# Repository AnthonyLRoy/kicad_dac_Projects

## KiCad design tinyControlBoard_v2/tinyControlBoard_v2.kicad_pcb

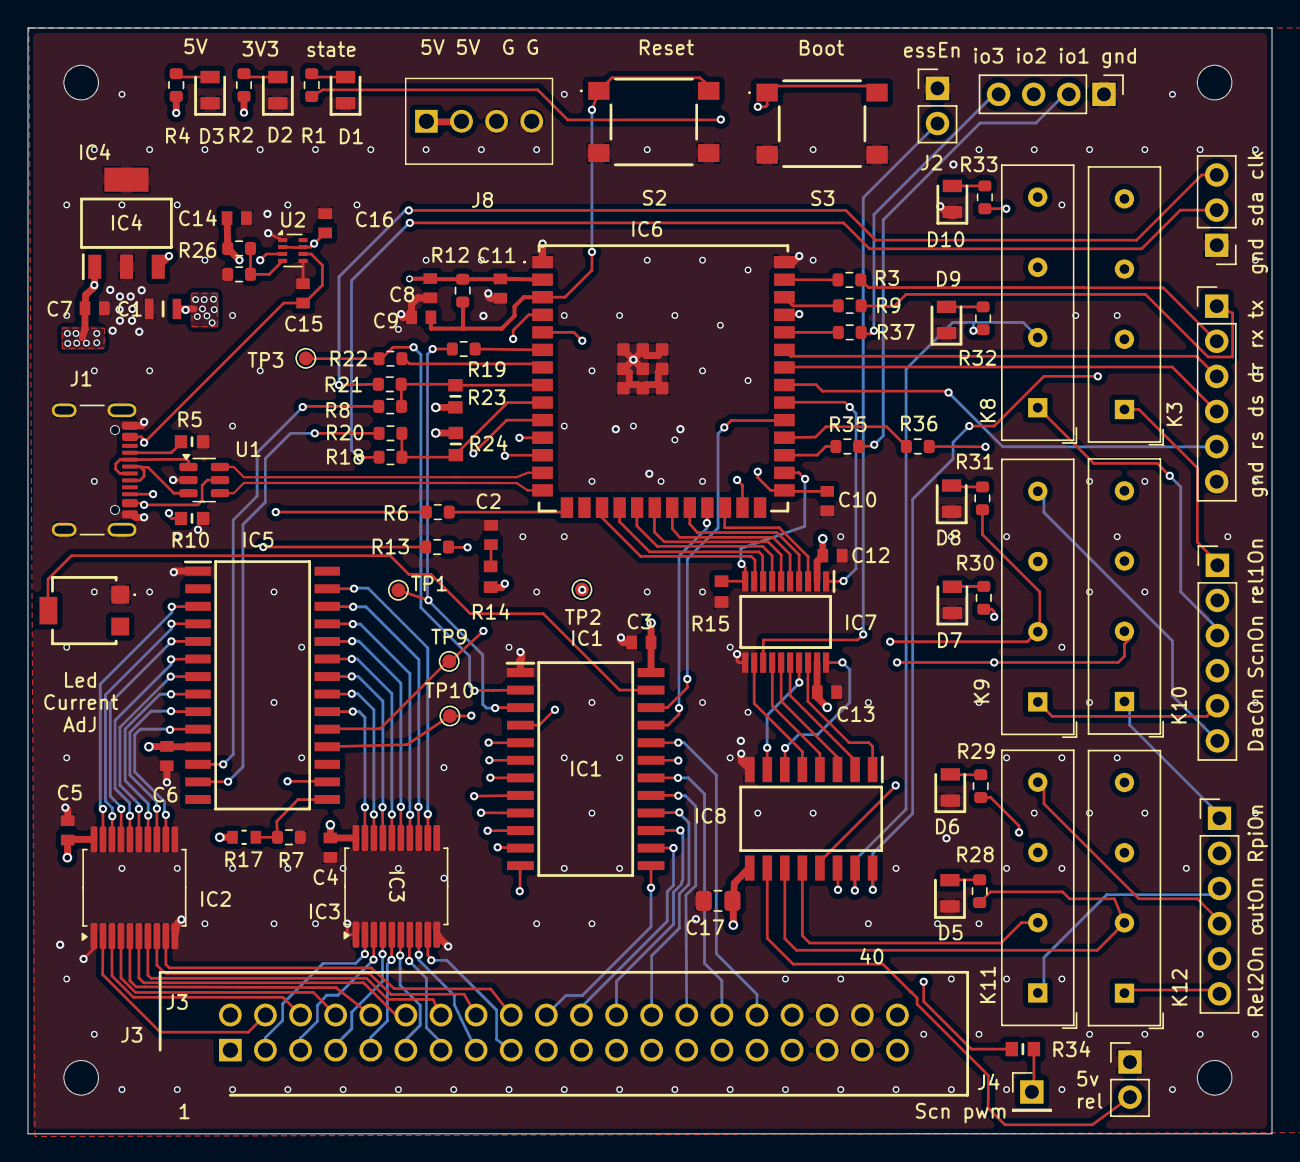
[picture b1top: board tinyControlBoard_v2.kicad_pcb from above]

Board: 6 copper layers, 90.0 x 80.0 mm, 99 parts (0 on the bottom side), 146 nets.

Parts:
C1: 33u; CAPC2012X145N
C2, C8: 10u; CAPC1608X90N
C3, C4, C5, C6, C9, C10, C11, C12, C13: 0u1; CAPC1608X87N
C7: 47u; CAPC1608X90N
C14, C15, C16: 1u; CAPC1608X90N
C17: 100n; C_0805_2012Metric_Pad1.18x1.45mm_HandSolder
D1, D2: LG_R971-KN-1; LEDC2012X80N
D3, D5, D6, D7, D8, D9, D10: LS_R976; LEDC2012X40N
H1, H2, H3, H4: MountingHole; MountingHole_2.5mm
IC1: STP16CPC26MTR; SOIC127P1032X265-24N
IC2, IC3: MAX6818EAP+T; SSOP-20_5.3x7.2mm_P0.65mm
IC4: LM3940IMPX-3.3; SOT230P700X180-4N
IC5: MCP23018-E_SO; SOIC127P1030X265-28N
IC6: ESP32-S3-WROOM-1U-N16; ESP32S3WROOM1UN16
IC7: TXS0108EPWRG4; SOP65P640X120-20N
IC8: ULN2003LVDR; SOIC127P780X200-16N
J1: USB_C_Receptacle_USB2.0_16P; USB_C_Receptacle_GCT_USB4105-xx-A_16P_TopMnt_Horizontal
J2, J11: Conn_01x02_Pin; PinHeader_1x02_P2.54mm_Vertical
J3: 70246-4001; SHDR40W64P254_2X20_5842X889X947P
J4: Conn_01x01_Socket; PinHeader_1x01_P2.54mm_Vertical
J5, J7, J9: Buffer; PinHeader_1x06_P2.54mm_Vertical
J6: Conn_01x04_Pin; PinHeader_1x04_P2.54mm_Vertical
J8: 1725672
J10: Conn_01x03_Pin; PinHeader_1x03_P2.54mm_Vertical
K3, K8, K9, K10, K11, K12: SIL05-1A72-71D; Relay_SPST_StandexMeder_SIL_Form1A
R1, R2: 100R; R_0603_1608Metric
R3, R8, R9, R18, R19, R20, R21, R22, R35, R36, R37: 22R; R_0603_1608Metric
R4, R6, R13: 300R; R_0603_1608Metric
R5, R10: 5K1; RESC1608X55N
R7: MCT0603PD1001DP500; R_0603_1608Metric
R12: 10K; R_0603_1608Metric
R14, R15: 10K; RESC1608X50N
R17: TNPW060315K0BEEA; RESC1608X60N
R23, R24: 4k7; RESC1609X55N
R25: 330k; R_0603_1608Metric
R26: 100k; R_0603_1608Metric
R28, R29, R30, R31, R32, R33: 1k; R_0603_1608Metric
R34: 22R; RESC1609X55N
S2, S3: 430182043816
TP1, TP2, TP3, TP9, TP10: S2761-46R; TestPoint_Pad_D1.0mm
U1: USBLC6-2SC6; SOT-23-6
U2: TPS2116DRL; SOT-583-8
VR1: 3214G-1-103E; 3214G1103E

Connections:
+3V3: C1.2, C3.2, C4.1, C5.2, C6.1, C8.1, C11.1, C12.1, IC1.24 (VDD), IC2.20 (VCC), IC3.20 (VCC), IC4.3 (OUT), IC5.11 (VDD), IC6.2 (3V3), IC7.2 (VCCA), R2.1, R12.1, R14.1, R17.1, R23.2, R24.2
+5V: C7.1, C13.1, C16.1, C17.2, IC4.1 (IN), IC7.19 (VCCB), IC8.9 (COM), J3.39, J3.40, K3.5, K8.5, K9.5, K10.5, K11.5, K12.5, R4.1, U2.2 (VOUT), U2.7 (VOUT)
/5v_io: IC6.22 (IO14), IC7.4 (A3)
/5v_io_ext: IC8.10 (OUT7), J11.2
/5v_io_out: IC7.17 (B3), IC8.7 (IN7)
/BOOT: C10.1, IC6.27 (IO0), S3.1 (COM_1), S3.3 (COM_2)
/EN: C9.1, IC6.3 (EN), R12.2, S2.1 (COM_1), S2.3 (COM_2)
/GPIO_01: IC6.39 (IO1), R3.1
/GPIO_02: IC6.38 (IO2), R9.1
/Gen2_on_ext: IC8.11 (OUT6), K12.3, R28.1
/Gen_1_on_ext: IC8.16 (OUT1), K3.3, R33.1
/Generic_io_1: IC6.29 (IO36), R35.1
/Generic_io_2: IC6.30 (IO37), R36.1
/Generic_io_3: IC6.36 (RXD0), R37.1
/I2c_sda_ext: J10.2, R18.1
/IntA: IC5.19 (INTA), IC6.11 (IO18), TP9.1 (1_1)
/Intb: IC5.18 (INTB), IC6.12 (IO8), TP10.1 (1_1)
/Serial Rx: J9.2, R3.2
/Serial Tx: J9.1, R9.2
/USB_5V: C15.1, J1.A4 (VBUS), J1.A9 (VBUS), J1.B4 (VBUS), J1.B9 (VBUS), U1.5 (VBUS), U2.6 (VIN2)
/USB_N: IC6.13 (IO19), U1.6 (I/O1)
/USB_P: IC6.14 (IO20), U1.4 (I/O2)
/addr_exp: IC5.15 (ADDR), R7.1, R17.2
/app_active: IC6.25 (IO48), R1.1
/btn_in_1: IC2.2 (IN1), J3.4
/btn_in_2: IC2.3 (IN2), J3.6
/btn_in_3: IC2.4 (IN3), J3.8
/btn_in_4: IC2.5 (IN4), J3.10
/btn_in_5: IC2.6 (IN5), J3.12
/btn_in_6: IC2.7 (IN6), J3.14
/btn_in_7: IC2.8 (IN7), J3.16
/btn_in_8: IC2.9 (IN8), J3.18
/btn_in_9: IC3.2 (IN1), J3.3
/btn_in_10: IC3.3 (IN2), J3.5
/btn_in_11: IC3.4 (IN3), J3.7
/btn_in_12: IC3.5 (IN4), J3.9
/btn_in_13: IC3.6 (IN5), J3.11
/btn_in_14: IC3.7 (IN6), J3.13
/btn_in_15: IC3.8 (IN7), J3.15
/btn_in_16: IC3.9 (IN8), J3.17
/btn_l_1: IC2.19 (OUT1), IC5.3 (GPB0)
/btn_l_2: IC2.18 (OUT2), IC5.4 (GPB1)
/btn_l_3: IC2.17 (OUT3), IC5.5 (GPB2)
/btn_l_4: IC2.16 (OUT4), IC5.6 (GPB3)
/btn_l_5: IC2.15 (OUT5), IC5.7 (GPB4)
/btn_l_6: IC2.14 (OUT6), IC5.8 (GPB5)
/btn_l_7: IC2.13 (OUT7), IC5.9 (GPB6)
/btn_l_8: IC2.12 (OUT8), IC5.10 (GPB7)
/btn_l_9: IC3.19 (OUT1), IC5.20 (GPA0)
/btn_l_10: IC3.18 (OUT2), IC5.21 (GPA1)
/btn_l_11: IC3.17 (OUT3), IC5.22 (GPA2)
/btn_l_12: IC3.16 (OUT4), IC5.23 (GPA3)
/btn_l_13: IC3.15 (OUT5), IC5.24 (GPA4)
/btn_l_14: IC3.14 (OUT6), IC5.25 (GPA5)
/btn_l_15: IC3.13 (OUT7), IC5.26 (GPA6)
/btn_l_16: IC3.12 (OUT8), IC5.27 (GPA7)
/dac_power: IC6.20 (IO12), IC7.6 (A5)
/dac_power_on_a: J5.5, K9.1
/dac_power_on_b: J5.6, K9.7
/dac_power_on_ext: IC8.14 (OUT3), K9.3, R31.1
/dac_power_out: IC7.15 (B5), IC8.3 (IN3)
/esp_ir_sent: IC6.34 (IO41), J9.4
/g_io_1: J6.2, R35.2
/g_io_2: J6.3, R36.2
/g_io_3: J6.4, R37.2
/gen2_a: J7.5, K12.7
/gen2_b: J7.6, K12.1
/gen_1_a: J5.1, K3.1
/gen_1_b: J5.2, K3.7
/i2c_clk: IC6.8 (IO15), R8.2, R21.2, R23.1
/i2c_clk_ext: J10.3, R21.1
/i2c_clk_int: IC5.12 (SCL), R8.1
/i2c_reset: IC5.16 (~RESET), IC6.10 (IO17)
/i2c_sda: IC6.9 (IO16), R18.2, R20.2, R24.1
/i2c_sda_int: IC5.13 (SDA), R20.1
/led_o_1: IC1.5 (OUT0), J3.19
/led_o_2: IC1.6 (OUT1), J3.21
/led_o_3: IC1.7 (OUT2), J3.23
/led_o_4: IC1.8 (OUT3), J3.25
/led_o_5: IC1.9 (OUT4), J3.27
/led_o_6: IC1.10 (OUT5), J3.29
/led_o_7: IC1.11 (OUT6), J3.31
/led_o_8: IC1.12 (OUT7), J3.33
/led_o_9: IC1.13 (OUT8), J3.20
/led_o_10: IC1.14 (OUT9), J3.22
/led_o_11: IC1.15 (OUT10), J3.24
/led_o_12: IC1.16 (OUT11), J3.26
/led_o_13: IC1.17 (OUT12), J3.28
/led_o_14: IC1.18 (OUT13), J3.30
/led_o_15: IC1.19 (OUT14), J3.34
/led_o_16: IC1.20 (OUT15), J3.32
/monitor_bright: IC6.37 (TXD0), R34.1
/on_led: IC6.15 (IO3), R6.1
/output_power_on_a: J7.3, K11.1
/output_power_on_b: J7.4, K11.7
/output_power_on_ext: IC8.12 (OUT5), K11.3, R29.1
/output_stage: IC6.17 (IO9), IC7.9 (A8)
/output_stage_out: IC7.12 (B8), IC8.5 (IN5)
/protodac_en: IC6.18 (IO10), IC7.8 (A7)
/protodac_en_out: IC7.13 (B7), J2.2
/relay_enable: IC6.28 (IO35), IC7.10 (OE), R15.1
/relay_gen_1: IC6.24 (IO47), IC7.3 (A2)
/relay_gen_1_out: IC7.18 (B2), IC8.1 (IN1)
/relay_gen_2: IC6.32 (IO39), IC7.1 (A1)
/relay_get_2_out: IC7.20 (B1), IC8.6 (IN6)
/rpi4_data_ready: IC6.35 (IO42), J9.3
/rpi_power: IC6.19 (IO11), IC7.7 (A6)
/rpi_power_on_a: J7.1, K10.1
/rpi_power_on_b: J7.2, K10.7
/rpi_power_on_ext: IC8.13 (OUT4), K10.3, R30.1
/rpi_power_out: IC7.14 (B6), IC8.4 (IN4)
/rpi_state: IC6.33 (IO40), J9.5
/screen_on: IC6.21 (IO13), IC7.5 (A4)
/screen_on_a: J5.3, K8.1
/screen_on_b: J5.4, K8.7
/screen_on_ext: IC8.15 (OUT2), K8.3, R32.1
/screen_on_out: IC7.16 (B4), IC8.2 (IN2)
/standby_led: IC6.4 (IO4), R13.2
/stp_clk: IC1.3 (CLK), R19.1, TP1.1 (1_1)
/stp_le: IC1.4 (LE), IC6.5 (IO5), TP2.1 (1_1)
/stp_pwm: IC1.21 (~OE), IC6.23 (IO21)
/stp_sdi: IC1.2 (SDI), R22.1, TP3.1 (1_1)
/stp_sdo: IC1.22 (SDO), IC6.31 (IO38)
GND: C1.1, C2.2, C3.1, C4.2, C5.1, C6.2, C7.2, C8.2, C9.2, C10.2, C11.2, C12.2, C13.2, C14.2, C15.2, C16.2, C17.1, D1.1 (K), D2.1 (K), D3.1 (K), D5.1 (K), D6.1 (K), D7.1 (K), D8.1 (K), D9.1 (K), D10.1 (K), IC1.1 (GND), IC2.1 (~EN), IC2.10 (GND), IC3.1 (~EN), IC3.10 (GND), IC4.2 (GND_1), IC4.4 (GND_2), IC5.1 (VSS), IC6.1 (GND_1), IC6.40 (GND_2), IC6.41 (GND_3), IC6.42 (GND_4), IC6.43 (GND_5), IC6.44 (GND_6), IC6.45 (GND_7), IC6.46 (GND_8), IC6.47 (GND_9), IC6.48 (GND_10), IC6.49 (GND_11), IC7.11 (GND), IC8.8 (GND), J1.A1 (GND), J1.A12 (GND), J1.B1 (GND), J1.B12 (GND), J1.S1 (SHIELD), J2.1, J3.35, J3.36, J3.37, J3.38, J6.1, J8.3, J8.4, J9.6, J10.1, J11.1, R5.2, R7.2, R10.2, R15.2, R26.1, S2.2 (NO_1), S2.4 (NO_2), S3.2 (NO_1), S3.4 (NO_2), U1.2 (GND), U2.1 (GND), U2.5 (MODE), VR1.1 (CCW)
unnamed: C2.1, R14.2
unnamed: D1.2 (A), R1.2
unnamed: D2.2 (A), R2.2
unnamed: D3.2 (A), R4.2
unnamed: D5.2 (A), R28.2
unnamed: D6.2 (A), R29.2
unnamed: D7.2 (A), R30.2
unnamed: D8.2 (A), R31.2
unnamed: D9.2 (A), R32.2
unnamed: D10.2 (A), R33.2
unnamed: IC1.23 (R-EXT), VR1.2 (WIPER)
unnamed: IC6.6 (IO6), R19.2
unnamed: IC6.7 (IO7), R22.2
unnamed: J1.A5 (CC1), R5.1
unnamed: J1.B5 (CC2), R10.1
unnamed: J1.A6 (D+), J1.B6 (D+), U1.3 (I/O2)
unnamed: J1.A7 (D-), J1.B7 (D-), U1.1 (I/O1)
unnamed: J3.1, R6.2
unnamed: J3.2, R13.1
unnamed: J4.1 (Pin_1_1), R34.2
unnamed: R25.2, R26.2, U2.4 (PR1)
VCC: C14.1, J8.1, J8.2, R25.1, U2.3 (VIN1)

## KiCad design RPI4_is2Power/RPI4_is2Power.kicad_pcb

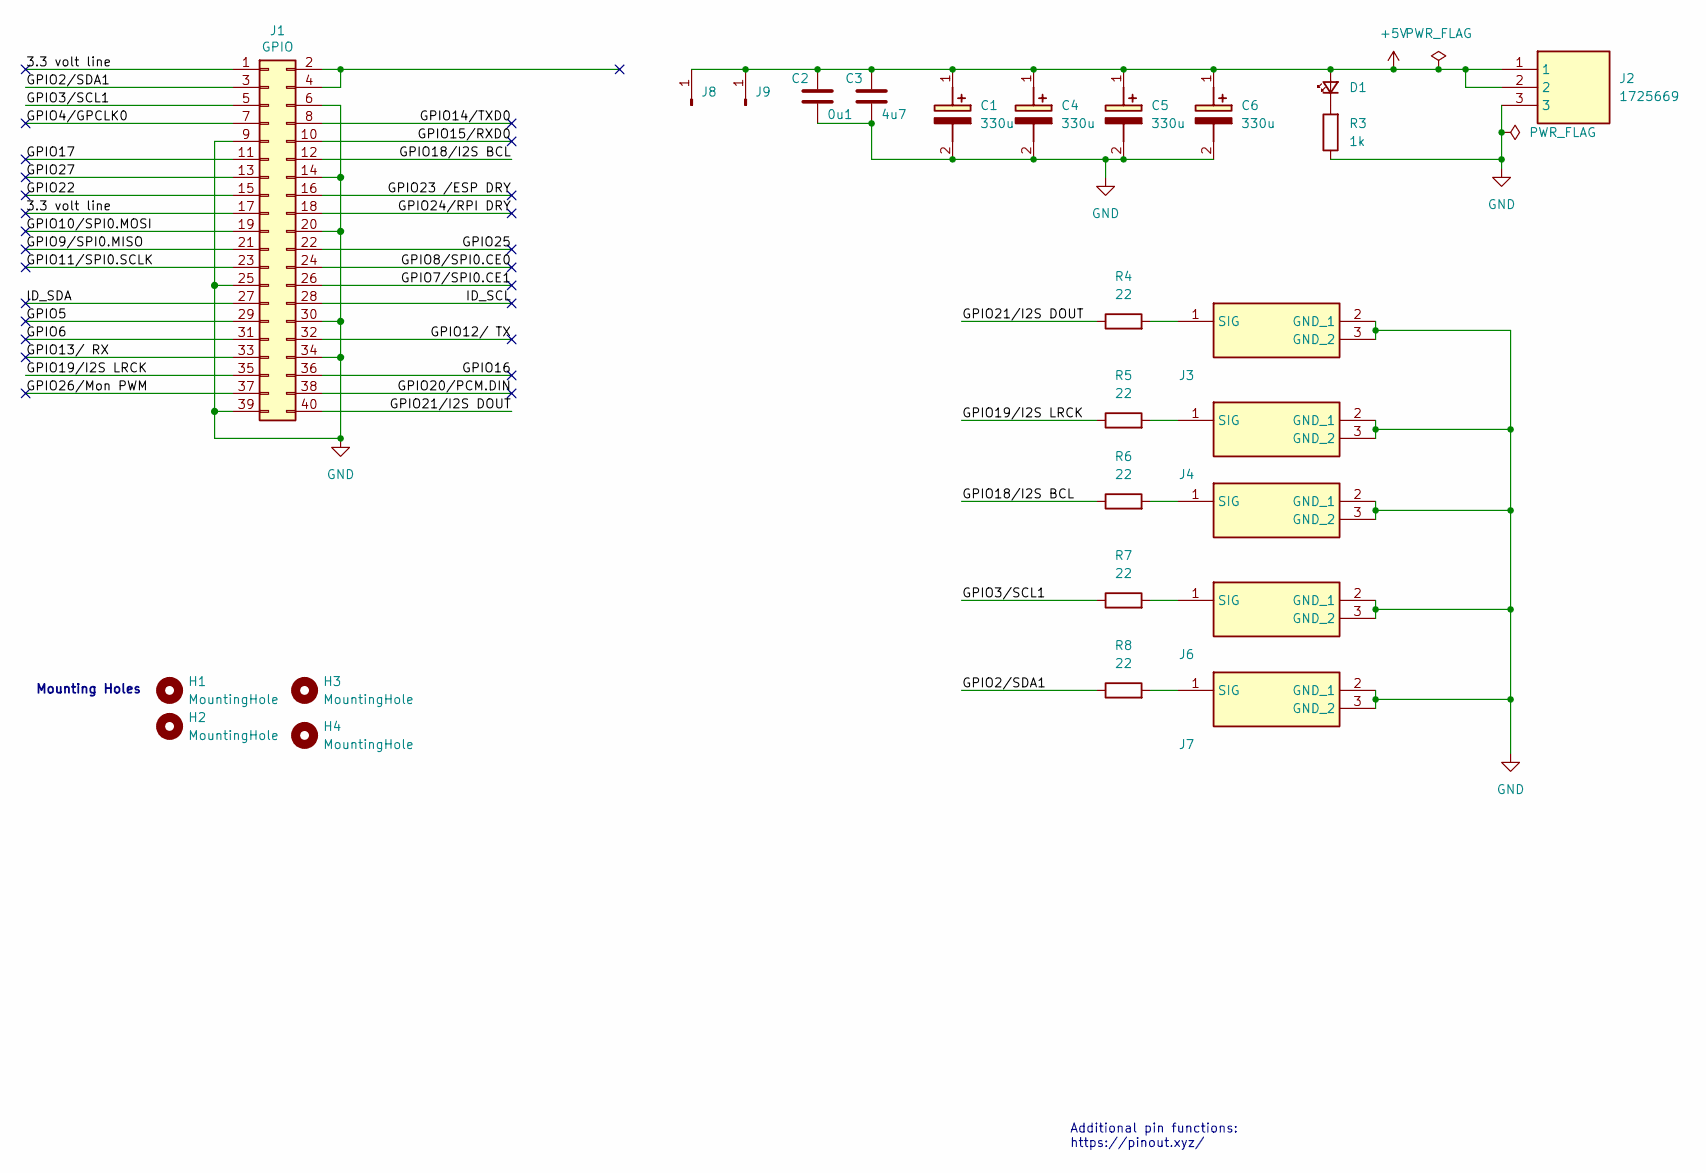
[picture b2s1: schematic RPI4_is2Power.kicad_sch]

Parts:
C1, C4, C5, C6: 330u; CAPPRD350W60D800H1300; Mouser Part Number 647-RNU1C331MDN1KX
C2: 0u1; C_0603_1608Metric_Pad1.08x0.95mm_HandSolder
C3: 4u7; CP_Radial_D5.0mm_P2.00mm
D1: LS_R976; LEDC2012X40N; Mouser Part Number 720-LSR976D5178
H1, H2, H3, H4: MountingHole; MountingHole_2.5mm
J1: GPIO; PinSocket_2x20_P2.54mm_Vertical
J2: 1725669; Mouser Part Number 651-1725669
J3, J4, J5, J6, J7: U.FL-R-SMT-1_80_; UFLRSMT180; Manufacturer_Part_Number U.FL-R-SMT-1(80)
J8, J9: Conn_01x01_Pin; Pin_D1.2mm_L11.3mm_W3.0mm_Flat
R3: 1k; R_0402_1005Metric
R4, R5, R6, R7, R8: 22; R_0402_1005Metric

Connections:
+5V: C1.1 (+), C2.1, C3.1, C4.1 (+), C5.1 (+), C6.1 (+), D1.2 (A), J2.1, J2.2, J8.1 (Pin_1_1), J9.1 (Pin_1_1)
/3.3 volt line: J1.1, J1.17
/GPIO2/SDA1: J1.3, R8.1
/GPIO3/SCL1: J1.5, R7.1
/GPIO4/GPCLK0: J1.7
/GPIO5: J1.29
/GPIO6: J1.31
/GPIO7/SPI0.CE1: J1.26
/GPIO8/SPI0.CE0: J1.24
/GPIO9/SPI0.MISO: J1.21
/GPIO10/SPI0.MOSI: J1.19
/GPIO11/SPI0.SCLK: J1.23
/GPIO12/ TX: J1.32
/GPIO13/ RX: J1.33
/GPIO14/TXD0: J1.8
/GPIO15/RXD0: J1.10
/GPIO16: J1.36
/GPIO17: J1.11
/GPIO18/I2S BCL: J1.12, R6.1
/GPIO19/I2S LRCK: J1.35, R5.1
/GPIO20/PCM.DIN: J1.38
/GPIO21/I2S DOUT: J1.40, R4.1
/GPIO22: J1.15
/GPIO23 /ESP DRY: J1.16
/GPIO24/RPI DRY: J1.18
/GPIO25: J1.22
/GPIO26/Mon PWM: J1.37
/GPIO27: J1.13
/ID_SCL: J1.28
/ID_SDA: J1.27
GND: C1.2 (-), C2.2, C3.2, C4.2 (-), C5.2 (-), C6.2 (-), J1.6, J1.9, J1.14, J1.20, J1.25, J1.30, J1.34, J1.39, J2.3, J3.2 (GND_1), J3.3 (GND_2), J4.2 (GND_1), J4.3 (GND_2), J5.2 (GND_1), J5.3 (GND_2), J6.2 (GND_1), J6.3 (GND_2), J7.2 (GND_1), J7.3 (GND_2), R3.1
unnamed: D1.1 (K), R3.2
unnamed: J3.1 (SIG), R4.2
unnamed: J4.1 (SIG), R5.2
unnamed: J5.1 (SIG), R6.2
unnamed: J6.1 (SIG), R7.2
unnamed: J7.1 (SIG), R8.2

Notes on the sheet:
Mounting Holes
Additional pin functions: https://pinout.xyz/

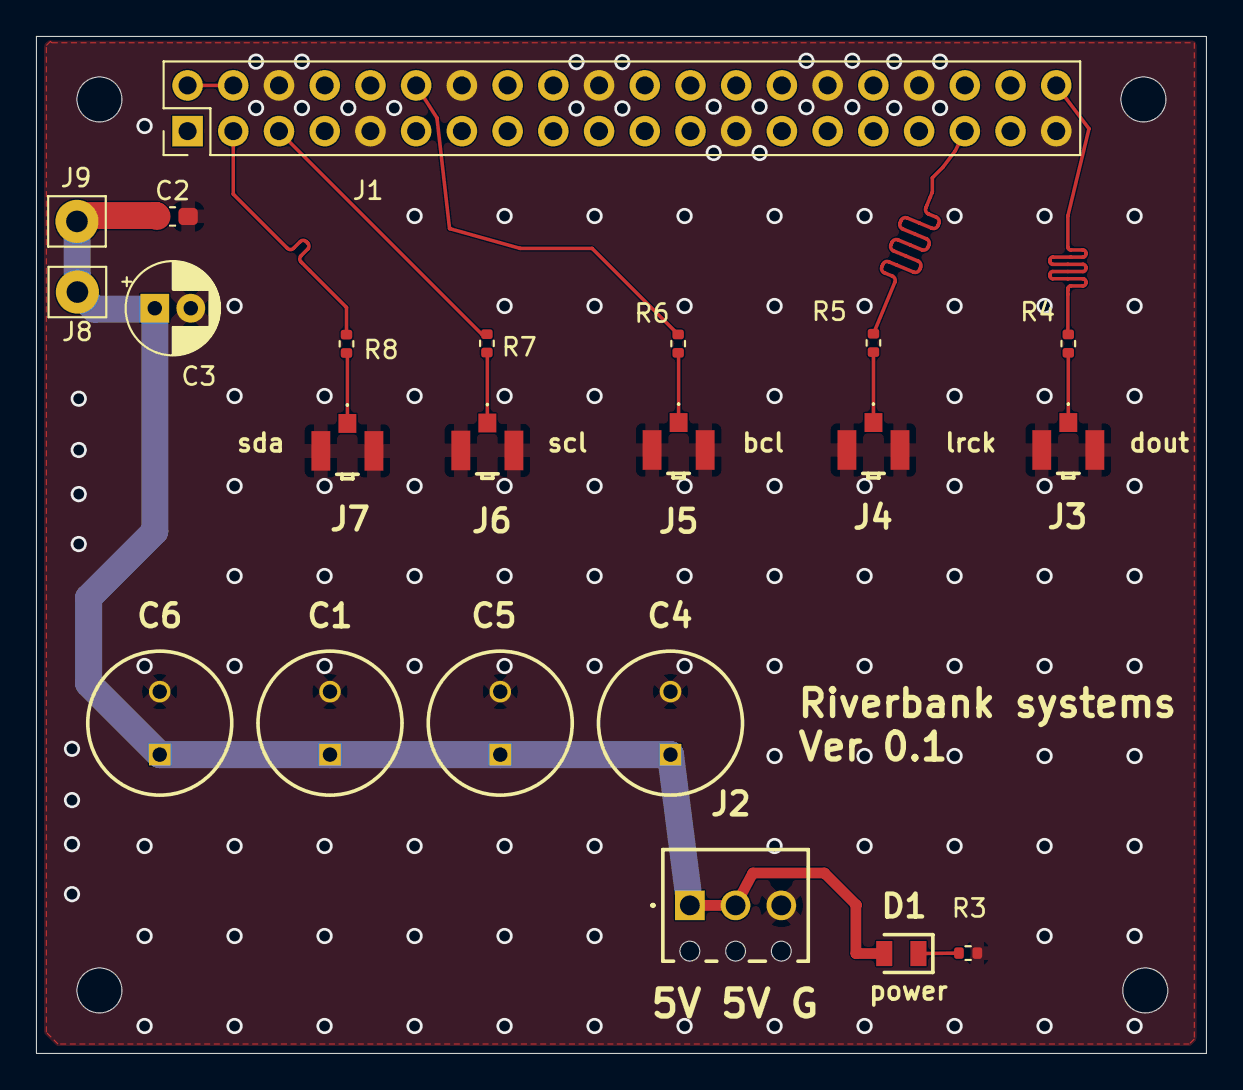
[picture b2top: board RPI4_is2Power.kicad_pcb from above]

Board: 2 copper layers, 65.0 x 56.5 mm, 26 parts (0 on the bottom side), 14 nets.

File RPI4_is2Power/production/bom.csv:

Designator,Footprint,Quantity,Value,LCSC Part #
"C1, C4, C5, C6",CAPPRD350W60D800H1300,4,330u,
C2,0603,1,0u1,
C3,CP_Radial_D5.0mm_P2.00mm,1,4u7,
D1,LEDC2012X40N,1,LS_R976,
"H1, H2, H3, H4",MountingHole_2.5mm,4,MountingHole,
J1,PinSocket_2x20_P2.54mm_Vertical,1,GPIO,
J2,1725669,1,1725669,
"J3, J4, J5, J6, J7",UFLRSMT180,5,U.FL-R-SMT-1_80_,
"J8, J9",Pin_D1.2mm_L11.3mm_W3.0mm_Flat,2,Conn_01x01_Pin,
R3,0402,1,1k,
"R4, R5, R6, R7, R8",0402,5,22,

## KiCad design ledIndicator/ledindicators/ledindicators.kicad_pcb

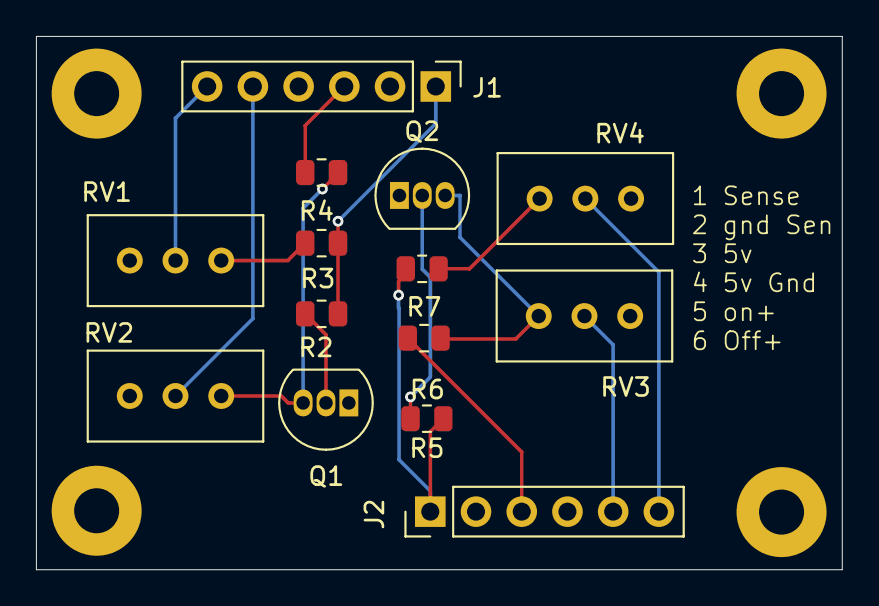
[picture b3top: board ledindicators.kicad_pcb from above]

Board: 2 copper layers, 44.8 x 29.6 mm, 18 parts (0 on the bottom side), 15 nets.

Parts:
H1, H2, H3, H4: MountingHole; MountingHole_2.5mm_Pad
J1, J2: Conn_01x06_Pin; PinHeader_1x06_P2.54mm_Vertical
Q1, Q2: 2N3904; TO-92_Inline
R2, R5: 10k; R_0805_2012Metric
R3, R4, R6, R7: 330R; R_0805_2012Metric
RV1, RV2, RV3, RV4: 100; Potentiometer_Bourns_3296W_Vertical

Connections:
GND: J1.2, J1.4, J2.2, J2.4, Q1.1 (E), Q2.1 (E)
unnamed: J1.1, R2.1, R3.2
unnamed: J1.3, R4.2
unnamed: J1.5, RV2.2
unnamed: J1.6, RV1.2
unnamed: J2.1, R5.1, R7.2
unnamed: J2.3, R6.2
unnamed: J2.5, RV3.2
unnamed: J2.6, RV4.2
unnamed: Q1.2 (B), R2.2
unnamed: Q1.3 (C), R4.1, RV2.1
unnamed: Q2.2 (B), R5.2
unnamed: Q2.3 (C), R6.1, RV3.1
unnamed: R3.1, RV1.1
unnamed: R7.1, RV4.1

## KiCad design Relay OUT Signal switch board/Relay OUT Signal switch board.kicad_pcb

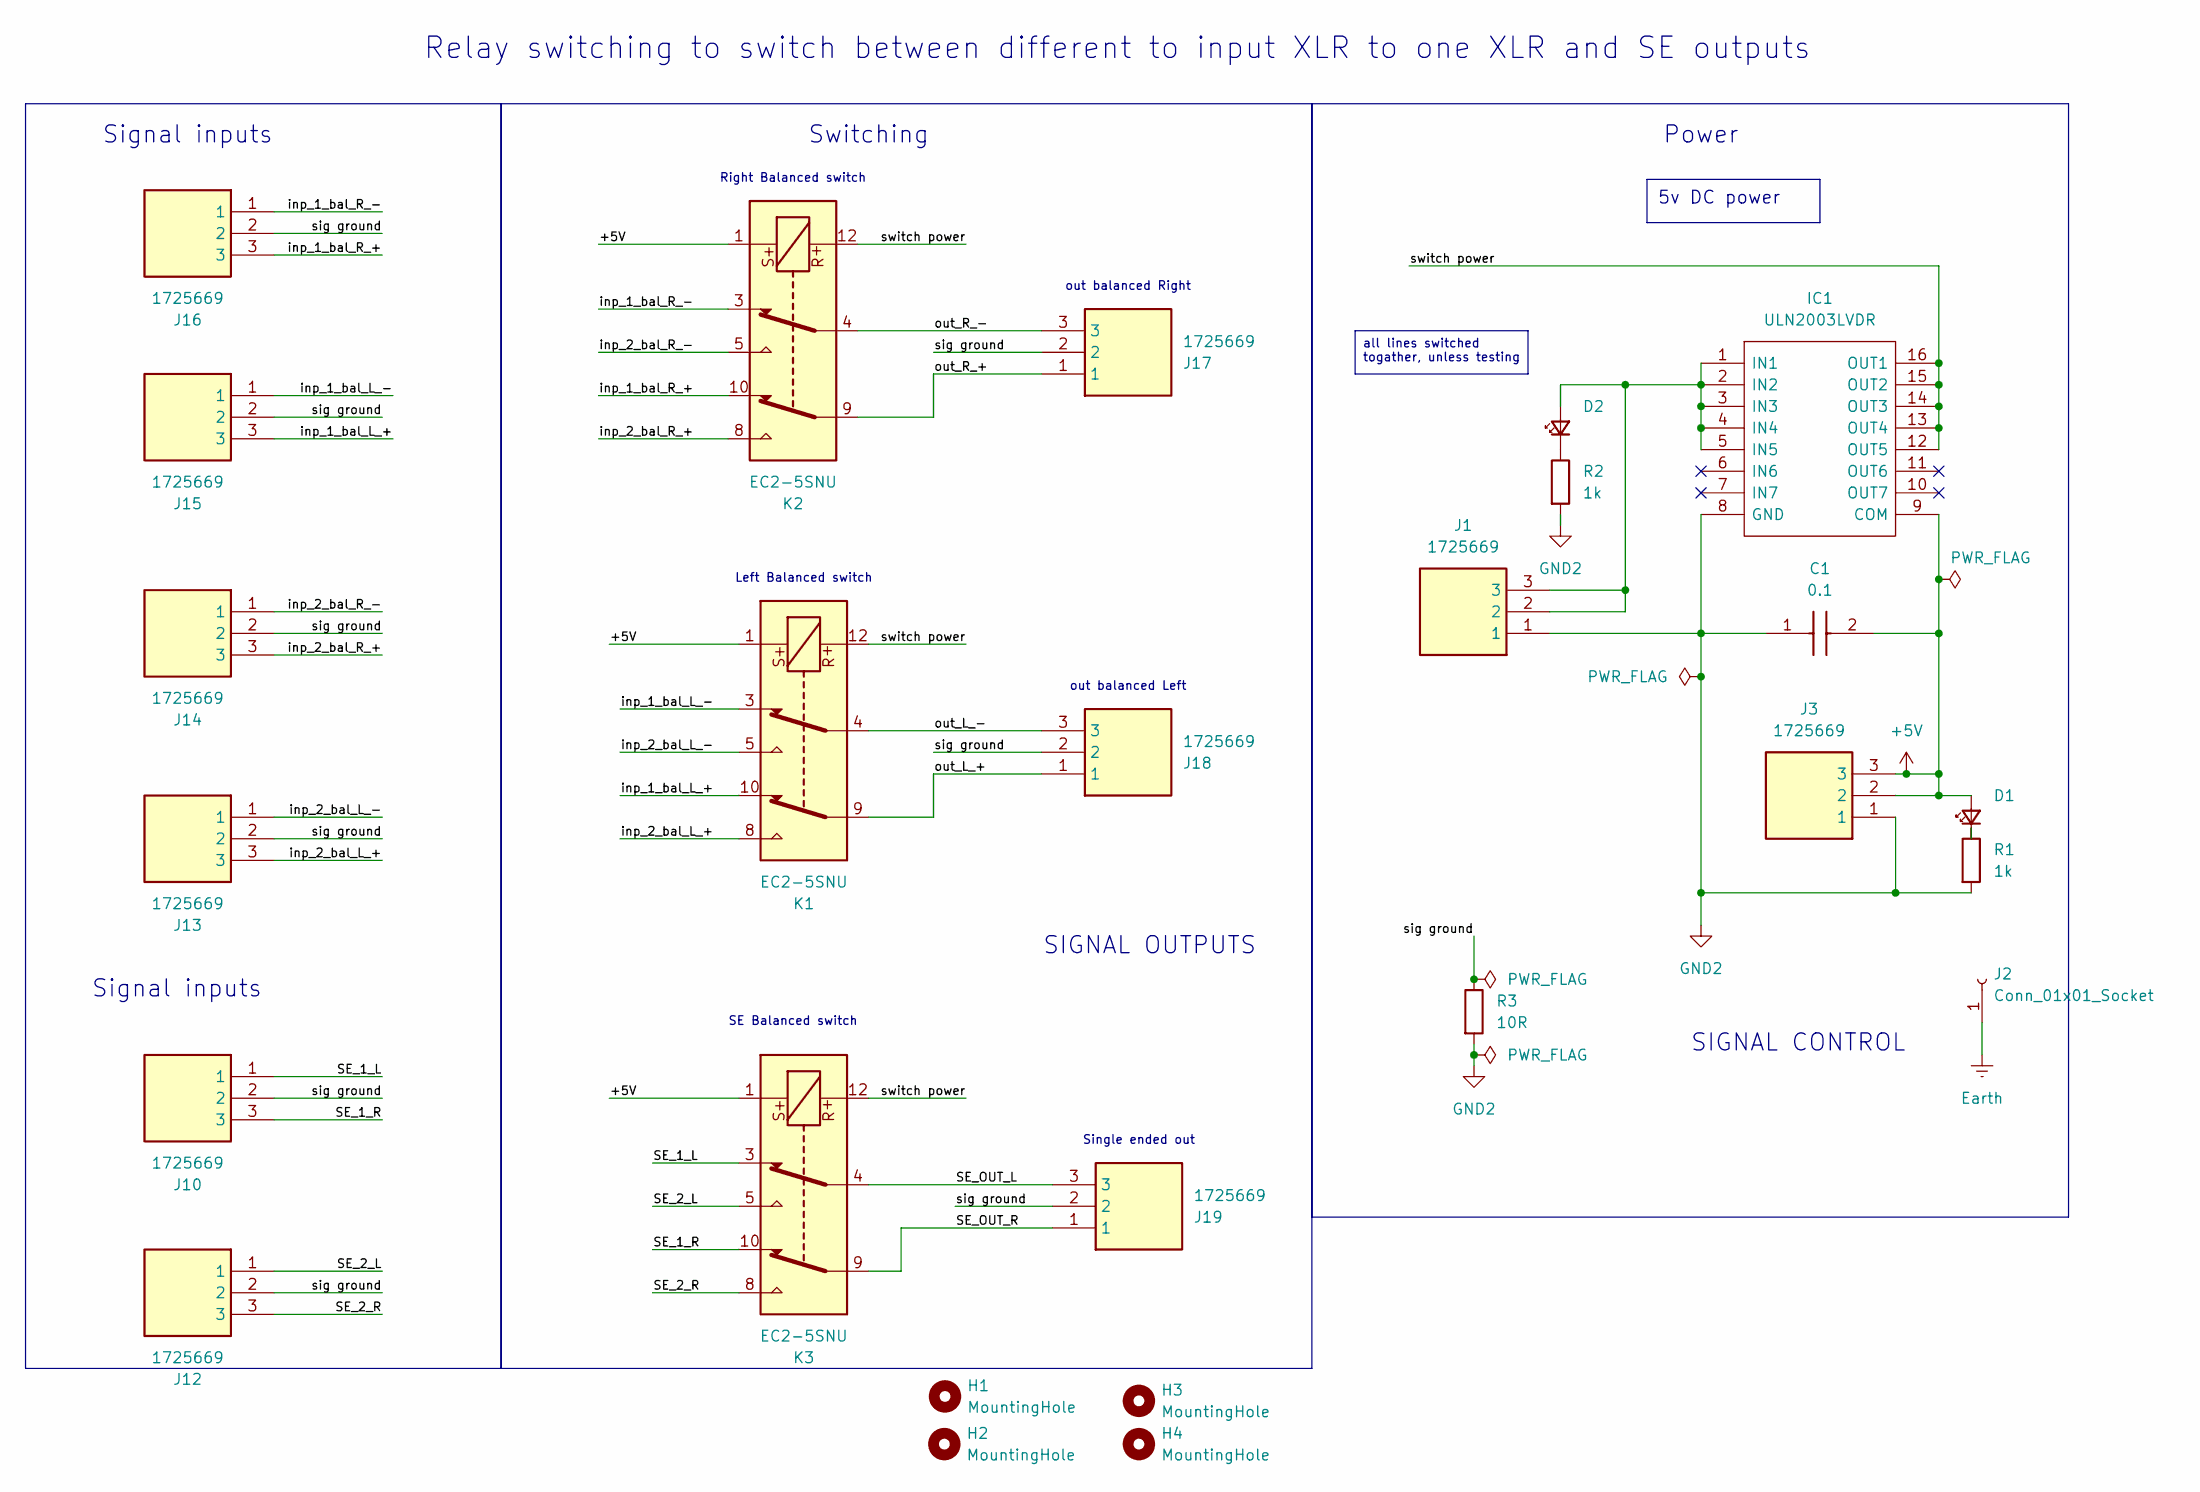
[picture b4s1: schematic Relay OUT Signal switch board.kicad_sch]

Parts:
C1: 0.1; C_0603_1608Metric; Mouser Part Number 80-C0603C104K4R3190
D1, D2: LS_R976; LEDC2012X40N; Mouser Part Number 720-LSR976D5178
H1, H2, H3, H4: MountingHole; MountingHole_2.5mm
IC1: ULN2003LVDR; SOIC127P780X200-16N; Manufacturer_Part_Number ULN2003LVDR; Mouser Part Number 595-ULN2003LVDR
J1, J3, J10, J12, J13, J14, J15, J16, J17, J18, J19: 1725669; Mouser Part Number 651-1725669
J2: Conn_01x01_Socket; PinHeader_1x01_P1.00mm_Vertical
K1, K2, K3: EC2-5SNU; Relay_DPDT_Kemet_EC2
R1, R2: 1k; R_0603_1608Metric
R3: 10R; R_0603_1608Metric

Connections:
+5V: C1.2, D1.2 (A), IC1.9 (COM), J3.2, J3.3, K1.1, K2.1, K3.1
/SE_1_L: J10.1, K3.3
/SE_1_R: J10.3, K3.10
/SE_2_L: J12.1, K3.5
/SE_2_R: J12.3, K3.8
/SE_OUT_L: J19.3, K3.4
/SE_OUT_R: J19.1, K3.9
/inp_1_bal_L_+: J15.3, K1.10
/inp_1_bal_L_-: J15.1, K1.3
/inp_1_bal_R_+: J16.3, K2.10
/inp_1_bal_R_-: J16.1, K2.3
/inp_2_bal_L_+: J13.3, K1.8
/inp_2_bal_L_-: J13.1, K1.5
/inp_2_bal_R_+: J14.3, K2.8
/inp_2_bal_R_-: J14.1, K2.5
/out_L_+: J18.1, K1.9
/out_L_-: J18.3, K1.4
/out_R_+: J17.1, K2.9
/out_R_-: J17.3, K2.4
/sig ground: J10.2, J12.2, J13.2, J14.2, J15.2, J16.2, J17.2, J18.2, J19.2, R3.1
Earth: J2.1
GND2: C1.1, IC1.8 (GND), J1.1, J3.1, R1.2, R2.2, R3.2
unnamed: D1.1 (K), R1.1
unnamed: D2.1 (K), R2.1

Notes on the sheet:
all lines switched togather, unless testing
5v DC power
out balanced Left
Left Balanced switch
Switching
Power
out balanced Right
Single ended out
Signal inputs
SIGNAL CONTROL
SE Balanced switch
Relay switching to switch between different to input XLR to one XLR and SE outputs
Right Balanced switch
SIGNAL OUTPUTS

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
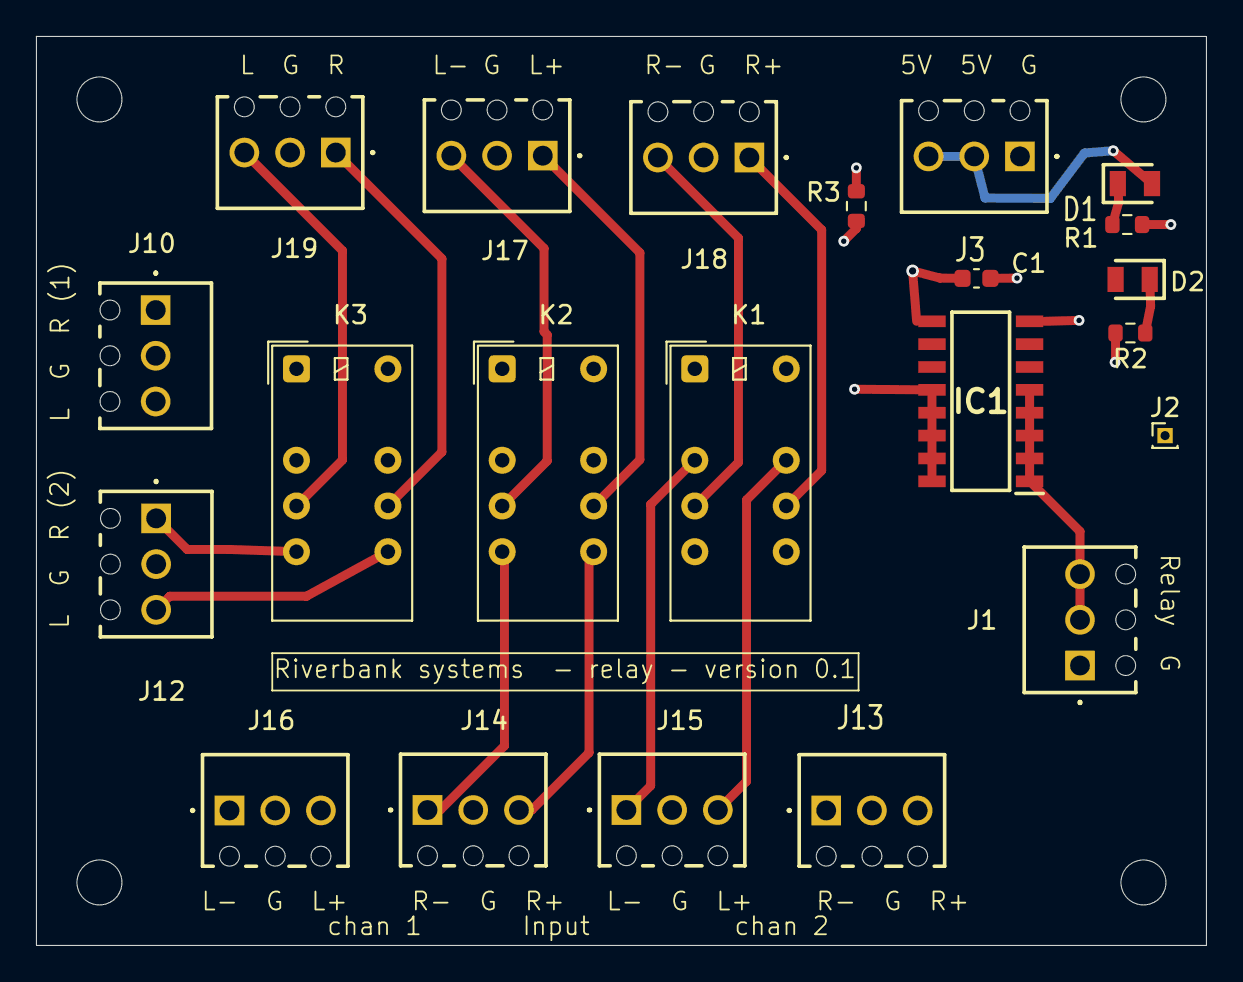
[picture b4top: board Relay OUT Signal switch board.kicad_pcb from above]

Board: 6 copper layers, 65.0 x 50.5 mm, 26 parts (0 on the bottom side), 25 nets.

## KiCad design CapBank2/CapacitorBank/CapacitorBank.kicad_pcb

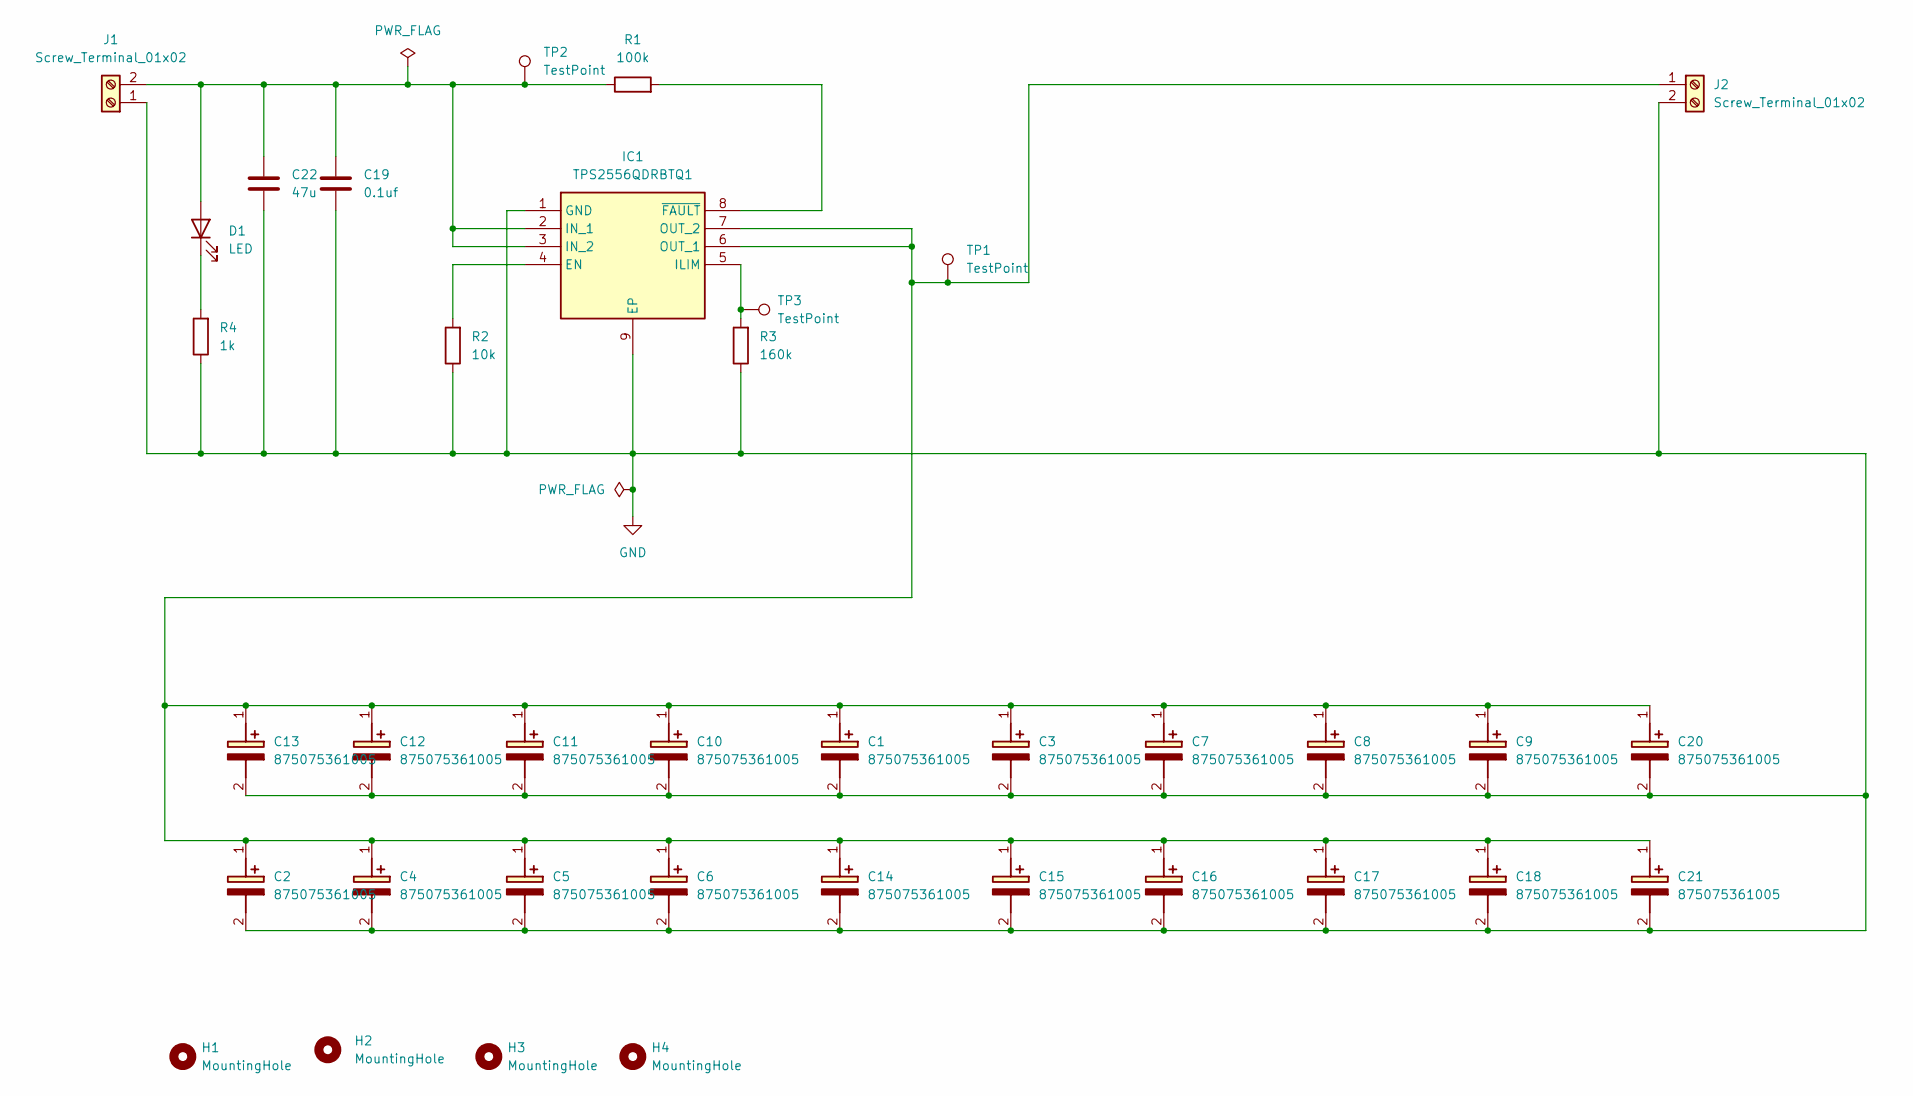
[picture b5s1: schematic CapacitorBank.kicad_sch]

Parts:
C1, C2, C3, C4, C5, C6, C7, C8, C9, C10, C11, C12, C13, C14, C15, C16, C17, C18, C20, C21: 875075361005; CAPAE1030X1270N; Mouser Part Number 710-875075361005
C19: 0.1uf; C_0805_2012Metric
C22: 47u; C_0805_2012Metric
D1: LED; LED_0603_1608Metric_Pad1.05x0.95mm_HandSolder
H1, H2, H3, H4: MountingHole; MountingHole_3.2mm_M3
IC1: TPS2556QDRBTQ1; SON65P300X300X100-9N-D; Mouser Part Number 595-TPS2556QDRBTQ1
J1, J2: Screw_Terminal_01x02; TerminalBlock_483132_2P_P7.62mm
R1: 100k; R_0805_2012Metric_Pad1.20x1.40mm_HandSolder
R2: 10k; R_0805_2012Metric_Pad1.20x1.40mm_HandSolder
R3: 160k; R_0805_2012Metric_Pad1.20x1.40mm_HandSolder
R4: 1k; R_0805_2012Metric_Pad1.20x1.40mm_HandSolder
TP1, TP2, TP3: TestPoint; TestPoint_Pad_1.5x1.5mm

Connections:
GND: C1.2 (-), C2.2 (-), C3.2 (-), C4.2 (-), C5.2 (-), C6.2 (-), C7.2 (-), C8.2 (-), C9.2 (-), C10.2 (-), C11.2 (-), C12.2 (-), C13.2 (-), C14.2 (-), C15.2 (-), C16.2 (-), C17.2 (-), C18.2 (-), C19.2, C20.2 (-), C21.2 (-), C22.2, IC1.1 (GND), IC1.9 (EP), J1.1, J2.2, R2.1, R3.1, R4.1
unnamed: C1.1 (+), C2.1 (+), C3.1 (+), C4.1 (+), C5.1 (+), C6.1 (+), C7.1 (+), C8.1 (+), C9.1 (+), C10.1 (+), C11.1 (+), C12.1 (+), C13.1 (+), C14.1 (+), C15.1 (+), C16.1 (+), C17.1 (+), C18.1 (+), C20.1 (+), C21.1 (+), IC1.6 (OUT_1), IC1.7 (OUT_2), J2.1, TP1.1
unnamed: C19.1, C22.1, D1.2 (A), IC1.2 (IN_1), IC1.3 (IN_2), J1.2, R1.1, TP2.1
unnamed: D1.1 (K), R4.2
unnamed: IC1.4 (EN), R2.2
unnamed: IC1.5 (ILIM), R3.2, TP3.1
unnamed: IC1.8 (~FAULT), R1.2
